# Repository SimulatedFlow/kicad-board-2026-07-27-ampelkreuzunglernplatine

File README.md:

# 2026-07-27-TrafficLightLearningBoard

<!-- SF-STORE-BLOCK:BEGIN -->
## 🛒 Source-available — see before you buy

This repository contains the **full design files** of a commercial hardware board. It is **source-available, not open source**: read it, evaluate it, then buy a license to use it. See **LICENSE.md (source-available, purchase required)**.

**Get it / Buy:**
- **Order on eBay** (this board, bare PCB): https://www.ebay.de/itm/398223890026
- Product page (specs, photos, price): https://simulatedflow.teufel-engineering.com/platinen/2026-07-27-ampelkreuzunglernplatine/
- eBay store — all our boards and PCB art: https://www.ebay.de/usr/simula-9
- Merch shop (dev & gaming): https://simulatedflow.myspreadshop.de
- Merch shop (Synthetica / EDM): https://synthetica.myspreadshop.de
- Direct / invoice (Simulated Flow UG): simulatedflow@gmail.com

### 📬 **Free Board Documentation & Firmware Pack**

Schematics, BOMs and example-firmware docs for our STM32 carrier boards. Get it by joining the newsletter — plus a heads-up when something new ships. Double opt-in, unsubscribe in one click, no address sharing.

👉 **[Get the free pack](https://simulatedflow.teufel-engineering.com/newsletter/hardware/?q=gh)**

_© 2026 Simulated Flow UG. All rights reserved._
<!-- SF-STORE-BLOCK:END -->

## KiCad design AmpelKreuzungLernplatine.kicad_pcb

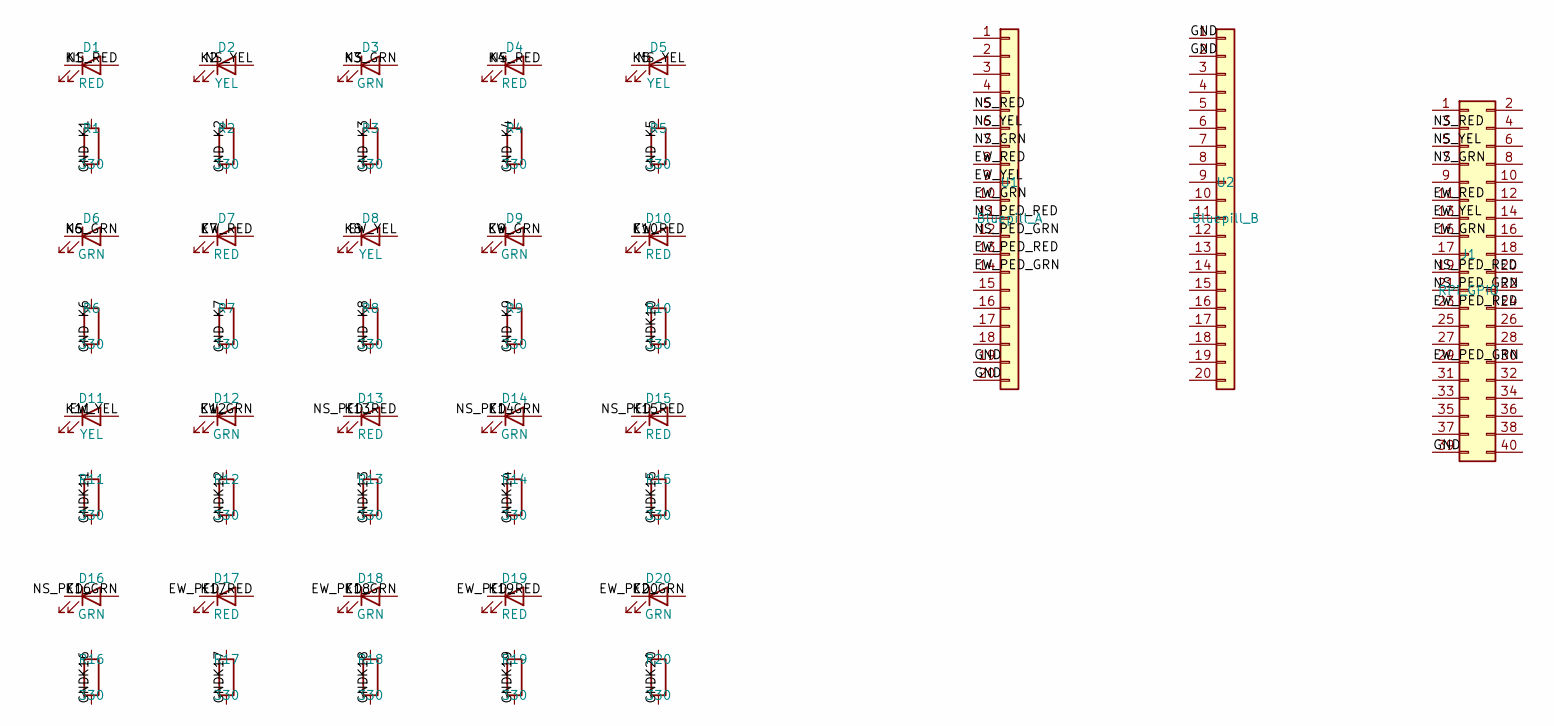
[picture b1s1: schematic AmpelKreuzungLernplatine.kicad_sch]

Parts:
D1, D4, D7, D10, D13, D15, D17, D19: RED; LED_D5.0mm
D2, D5, D8, D11: YEL; LED_D5.0mm
D3, D6, D9, D12, D14, D16, D18, D20: GRN; LED_D5.0mm
J1: RPi_GPIO; PinHeader_2x20_P2.54mm_Vertical
R1, R2, R3, R4, R5, R6, R7, R8, R9, R10, R11, R12, R13, R14, R15, R16, R17, R18, R19, R20: 330; R_0805_2012Metric
U1: Bluepill_A; PinSocket_1x20_P2.54mm_Vertical
U2: Bluepill_B; PinSocket_1x20_P2.54mm_Vertical

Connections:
EW_GRN: D9.2 (A), D12.2 (A), J1.15, U1.10
EW_PED_GRN: D18.2 (A), D20.2 (A), J1.29, U1.14
EW_PED_RED: D17.2 (A), D19.2 (A), J1.23, U1.13
EW_RED: D7.2 (A), D10.2 (A), J1.11, U1.8
EW_YEL: D8.2 (A), D11.2 (A), J1.13, U1.9
GND: J1.39, R1.2, R2.2, R3.2, R4.2, R5.2, R6.2, R7.2, R8.2, R9.2, R10.2, R11.2, R12.2, R13.2, R14.2, R15.2, R16.2, R17.2, R18.2, R19.2, R20.2, U1.19, U1.20, U2.1, U2.2
K1: D1.1 (K), R1.1
K2: D2.1 (K), R2.1
K3: D3.1 (K), R3.1
K4: D4.1 (K), R4.1
K5: D5.1 (K), R5.1
K6: D6.1 (K), R6.1
K7: D7.1 (K), R7.1
K8: D8.1 (K), R8.1
K9: D9.1 (K), R9.1
K10: D10.1 (K), R10.1
K11: D11.1 (K), R11.1
K12: D12.1 (K), R12.1
K13: D13.1 (K), R13.1
K14: D14.1 (K), R14.1
K15: D15.1 (K), R15.1
K16: D16.1 (K), R16.1
K17: D17.1 (K), R17.1
K18: D18.1 (K), R18.1
K19: D19.1 (K), R19.1
K20: D20.1 (K), R20.1
NS_GRN: D3.2 (A), D6.2 (A), J1.7, U1.7
NS_PED_GRN: D14.2 (A), D16.2 (A), J1.21, U1.12
NS_PED_RED: D13.2 (A), D15.2 (A), J1.19, U1.11
NS_RED: D1.2 (A), D4.2 (A), J1.3, U1.5
NS_YEL: D2.2 (A), D5.2 (A), J1.5, U1.6

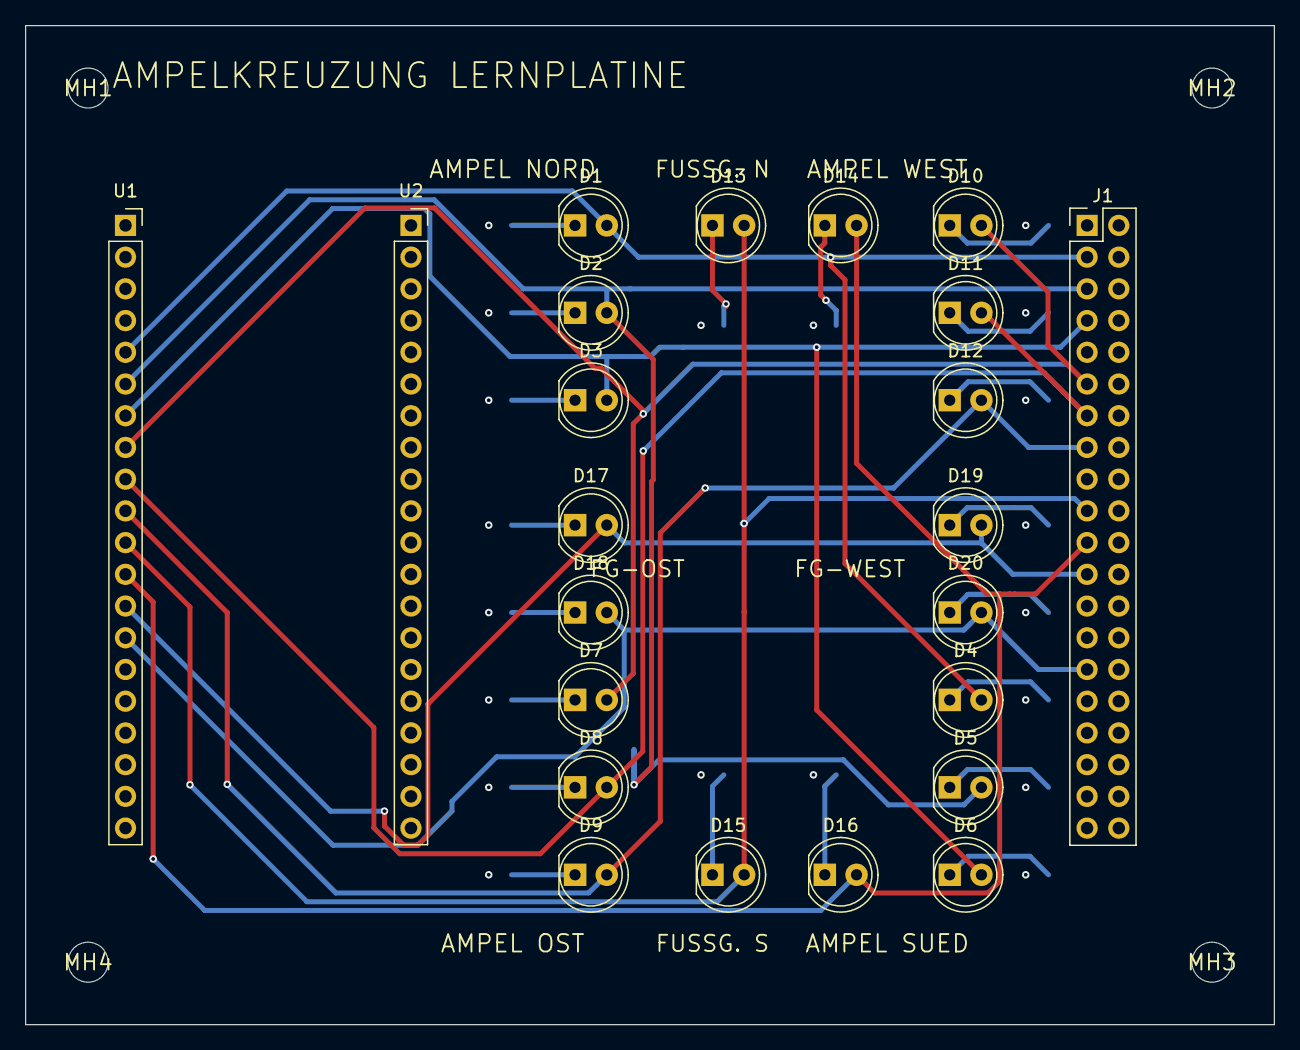
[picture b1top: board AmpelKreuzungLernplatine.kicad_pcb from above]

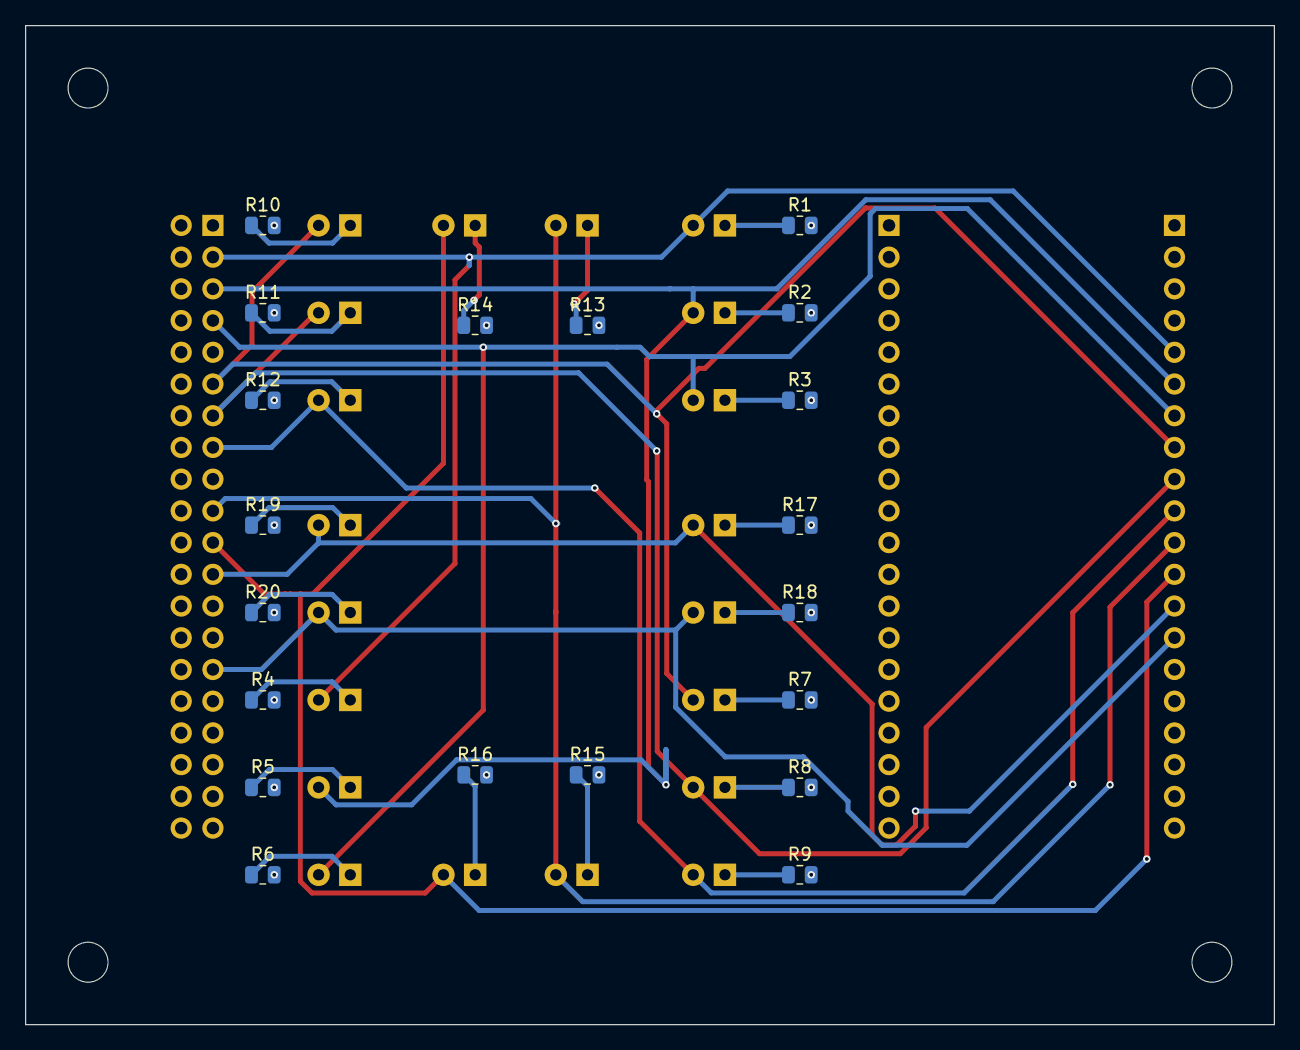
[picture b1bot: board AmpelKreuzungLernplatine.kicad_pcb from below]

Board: 4 copper layers, 100.0 x 80.0 mm, 47 parts (20 on the bottom side), 31 nets.

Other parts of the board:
MH1, MH2, MH3, MH4: MountingHole_3.2mm

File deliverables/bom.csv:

"Refs","Value","Footprint","Qty","DNP"
"D1","RED","LED_THT:LED_D5.0mm","1",""
"D2","YEL","LED_THT:LED_D5.0mm","1",""
"D3","GRN","LED_THT:LED_D5.0mm","1",""
"D4","RED","LED_THT:LED_D5.0mm","1",""
"D5","YEL","LED_THT:LED_D5.0mm","1",""
"D6","GRN","LED_THT:LED_D5.0mm","1",""
"D7","RED","LED_THT:LED_D5.0mm","1",""
"D8","YEL","LED_THT:LED_D5.0mm","1",""
"D9","GRN","LED_THT:LED_D5.0mm","1",""
"D10","RED","LED_THT:LED_D5.0mm","1",""
"D11","YEL","LED_THT:LED_D5.0mm","1",""
"D12","GRN","LED_THT:LED_D5.0mm","1",""
"D13","RED","LED_THT:LED_D5.0mm","1",""
"D14","GRN","LED_THT:LED_D5.0mm","1",""
"D15","RED","LED_THT:LED_D5.0mm","1",""
"D16","GRN","LED_THT:LED_D5.0mm","1",""
"D17","RED","LED_THT:LED_D5.0mm","1",""
"D18","GRN","LED_THT:LED_D5.0mm","1",""
"D19","RED","LED_THT:LED_D5.0mm","1",""
"D20","GRN","LED_THT:LED_D5.0mm","1",""
"J1","RPi_GPIO","Connector_PinHeader_2.54mm:PinHeader_2x20_P2.54mm_Vertical","1",""
"R1","330","Resistor_SMD:R_0805_2012Metric","1",""
"R2","330","Resistor_SMD:R_0805_2012Metric","1",""
"R3","330","Resistor_SMD:R_0805_2012Metric","1",""
"R4","330","Resistor_SMD:R_0805_2012Metric","1",""
"R5","330","Resistor_SMD:R_0805_2012Metric","1",""
"R6","330","Resistor_SMD:R_0805_2012Metric","1",""
"R7","330","Resistor_SMD:R_0805_2012Metric","1",""
"R8","330","Resistor_SMD:R_0805_2012Metric","1",""
"R9","330","Resistor_SMD:R_0805_2012Metric","1",""
"R10","330","Resistor_SMD:R_0805_2012Metric","1",""
"R11","330","Resistor_SMD:R_0805_2012Metric","1",""
"R12","330","Resistor_SMD:R_0805_2012Metric","1",""
"R13","330","Resistor_SMD:R_0805_2012Metric","1",""
"R14","330","Resistor_SMD:R_0805_2012Metric","1",""
"R15","330","Resistor_SMD:R_0805_2012Metric","1",""
"R16","330","Resistor_SMD:R_0805_2012Metric","1",""
"R17","330","Resistor_SMD:R_0805_2012Metric","1",""
"R18","330","Resistor_SMD:R_0805_2012Metric","1",""
"R19","330","Resistor_SMD:R_0805_2012Metric","1",""
"R20","330","Resistor_SMD:R_0805_2012Metric","1",""
"U1","Bluepill_A","Connector_PinSocket_2.54mm:PinSocket_1x20_P2.54mm_Vertical","1",""
"U2","Bluepill_B","Connector_PinSocket_2.54mm:PinSocket_1x20_P2.54mm_Vertical","1",""
